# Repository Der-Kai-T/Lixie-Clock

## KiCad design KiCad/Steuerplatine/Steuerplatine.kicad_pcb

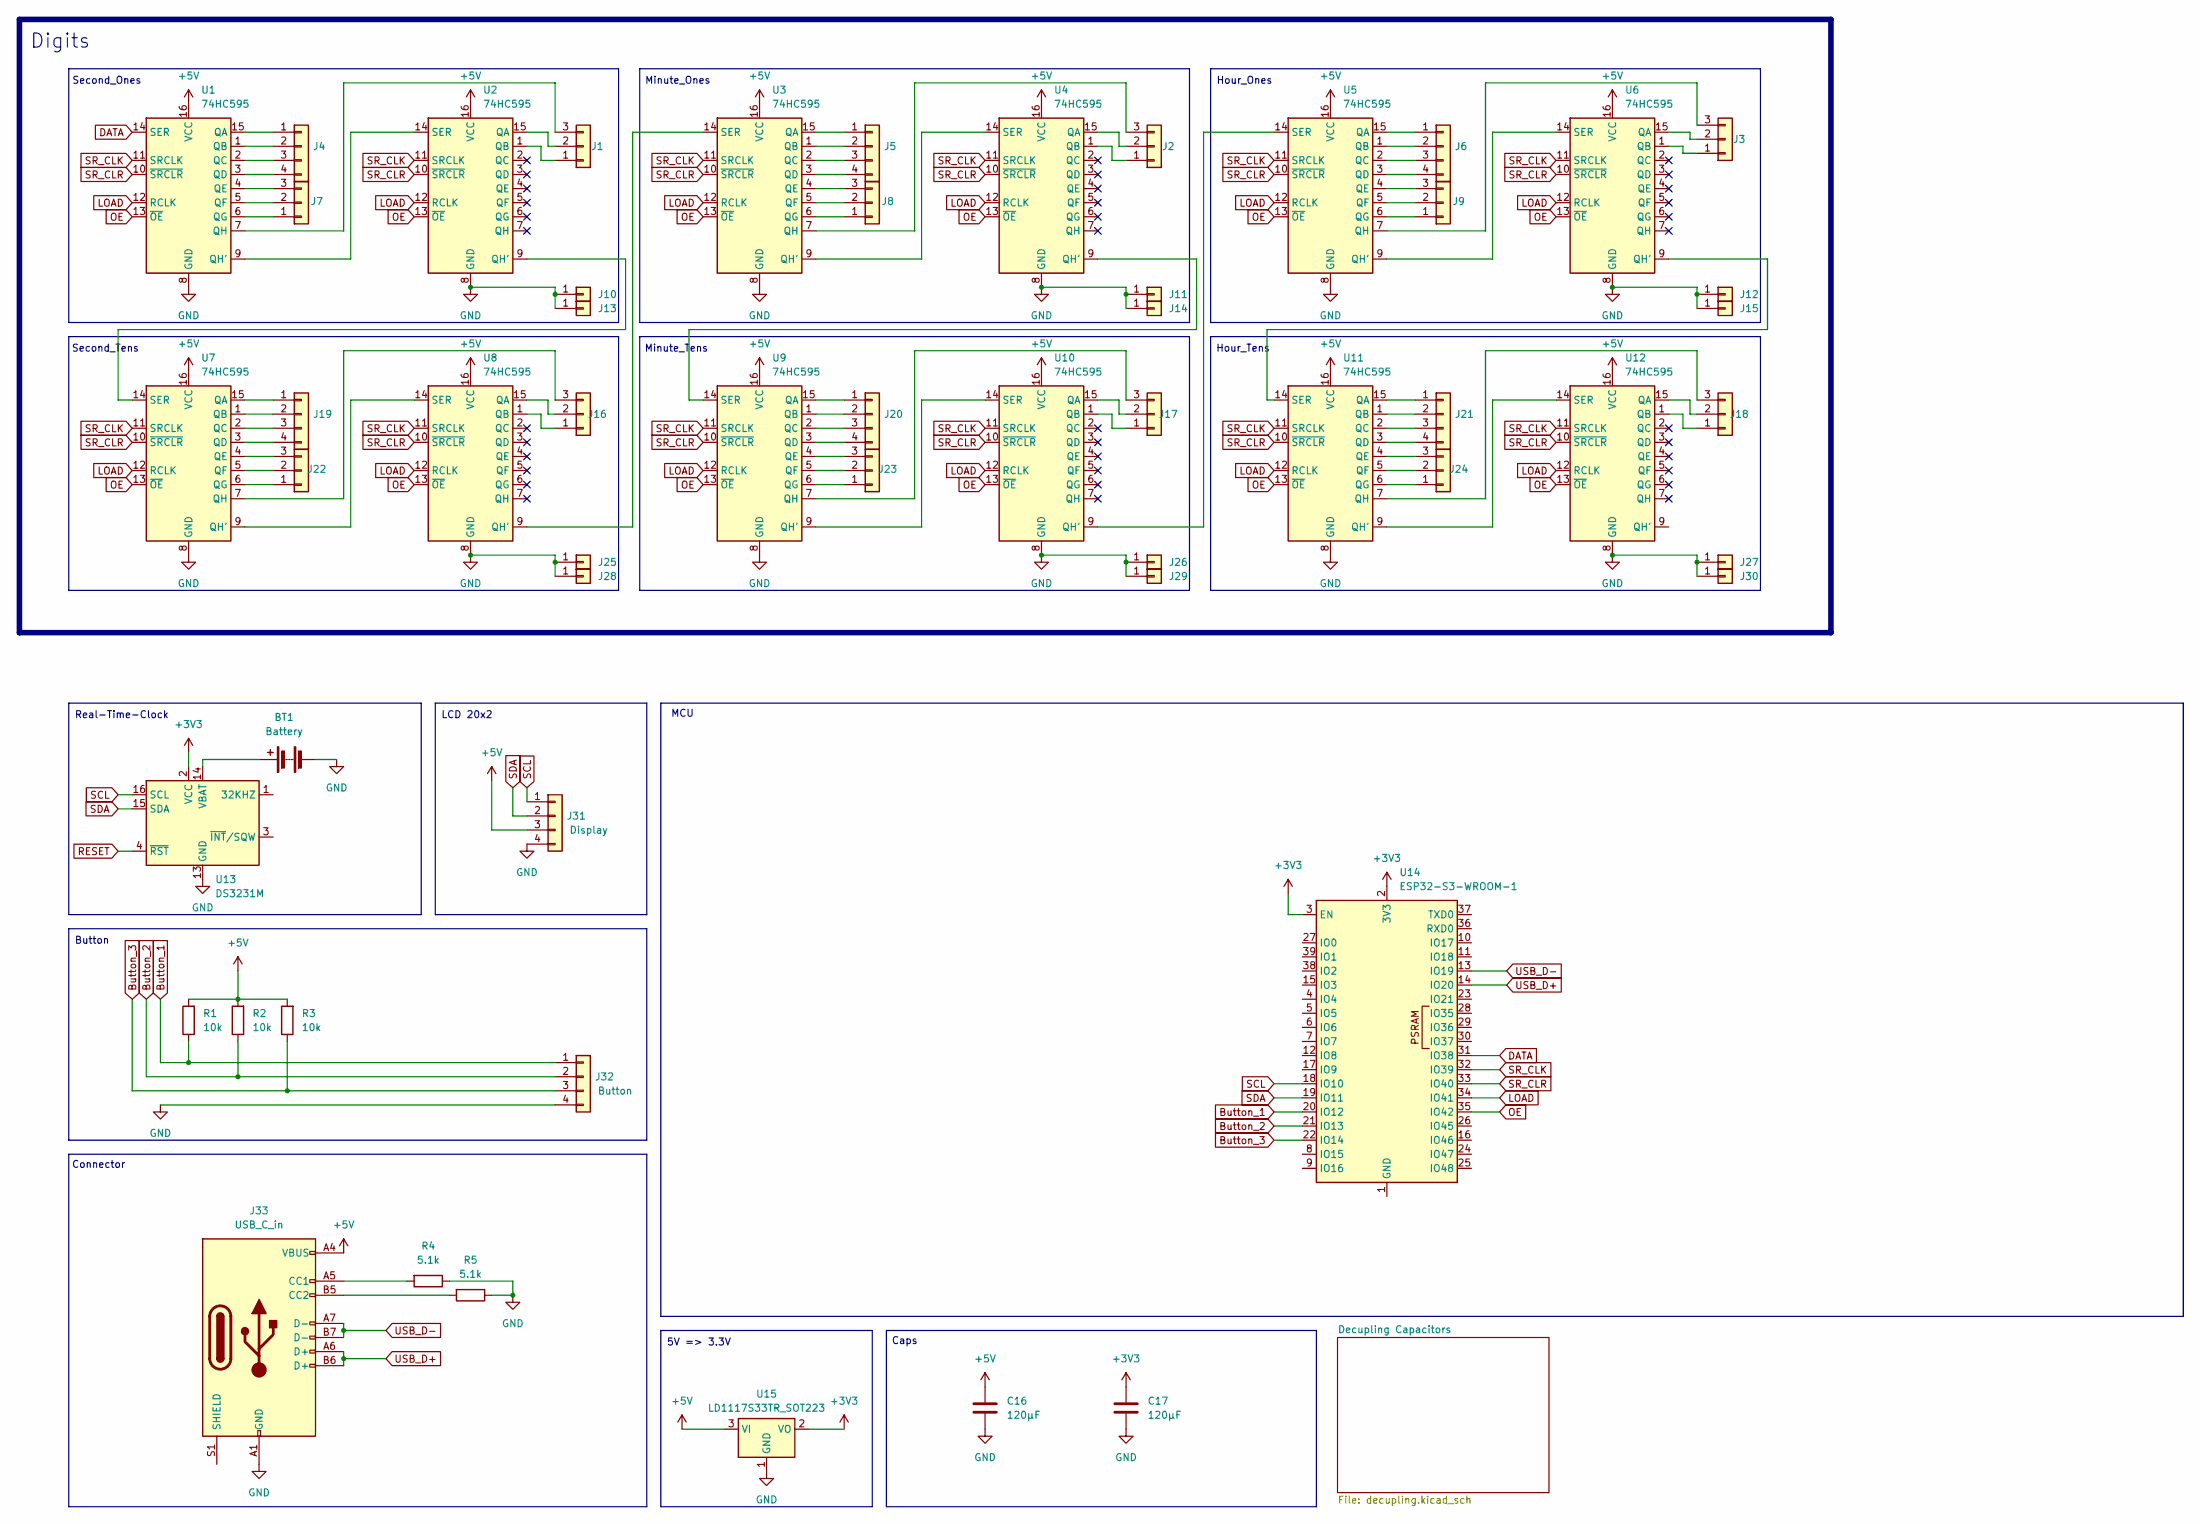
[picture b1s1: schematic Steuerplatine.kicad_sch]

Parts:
BT1: Battery; BatteryHolder_Multicomp_BC-2001_1x2032
C16, C17: 120µF; CP_Radial_D8.0mm_P3.50mm
J1, J2, J3, J7, J8, J9, J16, J17, J18, J22, J23, J24: Conn_01x03; PinSocket_1x03_P2.00mm_Vertical
J4, J5, J6, J19, J20, J21: Conn_01x04; PinSocket_1x04_P2.00mm_Vertical
J10, J11, J12, J13, J14, J15, J25, J26, J27, J28, J29, J30: GND; PinSocket_1x01_P2.00mm_Vertical
J31: Display; PinHeader_1x04_P2.54mm_Vertical
J32: Button; Molex_KK-254_AE-6410-04A_1x04_P2.54mm_Vertical
J33: USB_C_in; USB_C_Receptacle_GCT_USB4105-xx-A_16P_TopMnt_Horizontal
R1, R2, R3: 10k; R_1206_3216Metric_Pad1.30x1.75mm_HandSolder
R4, R5: 5.1k; R_1206_3216Metric_Pad1.30x1.75mm_HandSolder
U1, U2, U3, U4, U5, U6, U7, U8, U9, U10, U11, U12: 74HC595; SO-16_3.9x9.9mm_P1.27mm
U13: DS3231M; SOIC-16W_7.5x10.3mm_P1.27mm
U14: ESP32-S3-WROOM-1
U15: LD1117S33TR_SOT223; SOT-223-3_TabPin2

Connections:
+3V3: C17.1, U13.2 (VCC), U14.2 (3V3), U14.3 (EN), U15.2 (VO); also elsewhere on the board
+5V: C16.1, J31.3, J33.A4 (VBUS), J33.A9 (VBUS), J33.B4 (VBUS), J33.B9 (VBUS), R1.2, R2.2, R3.2, U1.16 (VCC), U2.16 (VCC), U3.16 (VCC), U4.16 (VCC), U5.16 (VCC), U6.16 (VCC), U7.16 (VCC), U8.16 (VCC), U9.16 (VCC), U10.16 (VCC), U11.16 (VCC), U12.16 (VCC), U15.3 (VI); also elsewhere on the board
Button_1: J32.1, R1.1, U14.20 (IO12)
Button_2: J32.2, R2.1, U14.21 (IO13)
Button_3: J32.3, R3.1, U14.22 (IO14)
DATA: U1.14 (SER), U14.31 (IO38)
GND: BT1.2 (-), C16.2, C17.2, J10.1, J11.1, J12.1, J13.1, J14.1, J15.1, J25.1, J26.1, J27.1, J28.1, J29.1, J30.1, J31.4, J32.4, J33.A1 (GND), J33.A12 (GND), J33.B1 (GND), J33.B12 (GND), R4.1, R5.1, U1.8 (GND), U2.8 (GND), U3.8 (GND), U4.8 (GND), U5.8 (GND), U6.8 (GND), U7.8 (GND), U8.8 (GND), U9.8 (GND), U10.8 (GND), U11.8 (GND), U12.8 (GND), U13.5 (GND), U13.6 (GND), U13.7 (GND), U13.8 (GND), U13.9 (GND), U13.10 (GND), U13.11 (GND), U13.12 (GND), U13.13 (GND), U15.1 (GND); also elsewhere on the board
LOAD: U1.12 (RCLK), U2.12 (RCLK), U3.12 (RCLK), U4.12 (RCLK), U5.12 (RCLK), U6.12 (RCLK), U7.12 (RCLK), U8.12 (RCLK), U9.12 (RCLK), U10.12 (RCLK), U11.12 (RCLK), U12.12 (RCLK), U14.34 (IO41)
unnamed: BT1.1 (+), U13.14 (VBAT)
unnamed: J1.1, U2.1 (QB)
unnamed: J1.2, U2.15 (QA)
unnamed: J1.3, U1.7 (QH)
unnamed: J2.1, U4.1 (QB)
unnamed: J2.2, U4.15 (QA)
unnamed: J2.3, U3.7 (QH)
unnamed: J3.1, U6.1 (QB)
unnamed: J3.2, U6.15 (QA)
unnamed: J3.3, U5.7 (QH)
unnamed: J4.1, U1.15 (QA)
unnamed: J4.2, U1.1 (QB)
unnamed: J4.3, U1.2 (QC)
unnamed: J4.4, U1.3 (QD)
unnamed: J5.1, U3.15 (QA)
unnamed: J5.2, U3.1 (QB)
unnamed: J5.3, U3.2 (QC)
unnamed: J5.4, U3.3 (QD)
unnamed: J6.1, U5.15 (QA)
unnamed: J6.2, U5.1 (QB)
unnamed: J6.3, U5.2 (QC)
unnamed: J6.4, U5.3 (QD)
unnamed: J7.1, U1.6 (QG)
unnamed: J7.2, U1.5 (QF)
unnamed: J7.3, U1.4 (QE)
unnamed: J8.1, U3.6 (QG)
unnamed: J8.2, U3.5 (QF)
unnamed: J8.3, U3.4 (QE)
unnamed: J9.1, U5.6 (QG)
unnamed: J9.2, U5.5 (QF)
unnamed: J9.3, U5.4 (QE)
unnamed: J16.1, U8.1 (QB)
unnamed: J16.2, U8.15 (QA)
unnamed: J16.3, U7.7 (QH)
unnamed: J17.1, U10.1 (QB)
unnamed: J17.2, U10.15 (QA)
unnamed: J17.3, U9.7 (QH)
unnamed: J18.1, U12.1 (QB)
unnamed: J18.2, U12.15 (QA)
unnamed: J18.3, U11.7 (QH)
unnamed: J19.1, U7.15 (QA)
unnamed: J19.2, U7.1 (QB)
unnamed: J19.3, U7.2 (QC)
unnamed: J19.4, U7.3 (QD)
unnamed: J20.1, U9.15 (QA)
unnamed: J20.2, U9.1 (QB)
unnamed: J20.3, U9.2 (QC)
unnamed: J20.4, U9.3 (QD)
unnamed: J21.1, U11.15 (QA)
unnamed: J21.2, U11.1 (QB)
unnamed: J21.3, U11.2 (QC)
unnamed: J21.4, U11.3 (QD)
unnamed: J22.1, U7.6 (QG)
unnamed: J22.2, U7.5 (QF)
unnamed: J22.3, U7.4 (QE)
unnamed: J23.1, U9.6 (QG)
unnamed: J23.2, U9.5 (QF)
unnamed: J23.3, U9.4 (QE)
unnamed: J24.1, U11.6 (QG)
unnamed: J24.2, U11.5 (QF)
unnamed: J24.3, U11.4 (QE)
unnamed: J33.A5 (CC1), R4.2
unnamed: J33.B5 (CC2), R5.2
unnamed: U1.9 (QH'), U2.14 (SER)
unnamed: U2.9 (QH'), U7.14 (SER)
unnamed: U3.9 (QH'), U4.14 (SER)
unnamed: U3.14 (SER), U8.9 (QH')
unnamed: U4.9 (QH'), U9.14 (SER)
unnamed: U5.9 (QH'), U6.14 (SER)
unnamed: U7.9 (QH'), U8.14 (SER)
unnamed: U5.14 (SER), U10.9 (QH')
unnamed: U9.9 (QH'), U10.14 (SER)
unnamed: U11.9 (QH'), U12.14 (SER)
unnamed: U6.9 (QH'), U11.14 (SER)
unnamed: U14.1 (GND), U14.40 (GND), U14.41 (GND)
OE: U1.13 (~OE), U2.13 (~OE), U3.13 (~OE), U4.13 (~OE), U5.13 (~OE), U6.13 (~OE), U7.13 (~OE), U8.13 (~OE), U9.13 (~OE), U10.13 (~OE), U11.13 (~OE), U12.13 (~OE), U14.35 (IO42)
RESET: U13.4 (~RST)
SCL: J31.1, U13.16 (SCL), U14.18 (IO10)
SDA: J31.2, U13.15 (SDA), U14.19 (IO11)
SR_CLK: U1.11 (SRCLK), U2.11 (SRCLK), U3.11 (SRCLK), U4.11 (SRCLK), U5.11 (SRCLK), U6.11 (SRCLK), U7.11 (SRCLK), U8.11 (SRCLK), U9.11 (SRCLK), U10.11 (SRCLK), U11.11 (SRCLK), U12.11 (SRCLK), U14.32 (IO39)
SR_CLR: U1.10 (~SRCLR), U2.10 (~SRCLR), U3.10 (~SRCLR), U4.10 (~SRCLR), U5.10 (~SRCLR), U6.10 (~SRCLR), U7.10 (~SRCLR), U8.10 (~SRCLR), U9.10 (~SRCLR), U10.10 (~SRCLR), U11.10 (~SRCLR), U12.10 (~SRCLR), U14.33 (IO40)
USB_D+: J33.A6 (D+), J33.B6 (D+), U14.14 (IO20)
USB_D-: J33.A7 (D-), J33.B7 (D-), U14.13 (IO19)

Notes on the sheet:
5V => 3.3V
Caps
Button
Hour_Tens
LCD 20x2
Digits
Connector
Minute_Ones
Minute_Tens
Second_Ones
Second_Tens
Hour_Ones
Real-Time-Clock
MCU

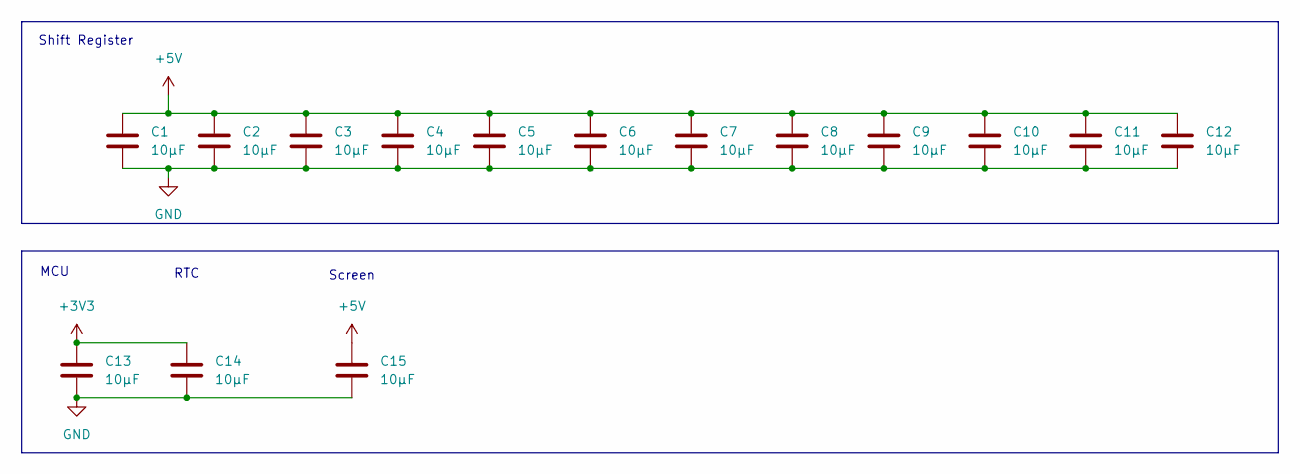
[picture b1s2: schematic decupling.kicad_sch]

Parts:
C1, C2, C3, C4, C5, C6, C7, C8, C9, C10, C11, C12, C13, C14, C15: 10µF; C_0805_2012Metric

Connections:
+3V3: C13.1, C14.1; also elsewhere on the board
+5V: C1.1, C2.1, C3.1, C4.1, C5.1, C6.1, C7.1, C8.1, C9.1, C10.1, C11.1, C12.1, C15.1; also elsewhere on the board
GND: C1.2, C2.2, C3.2, C4.2, C5.2, C6.2, C7.2, C8.2, C9.2, C10.2, C11.2, C12.2, C13.2, C14.2, C15.2; also elsewhere on the board

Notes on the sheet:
Shift Register
MCU
RTC
Screen

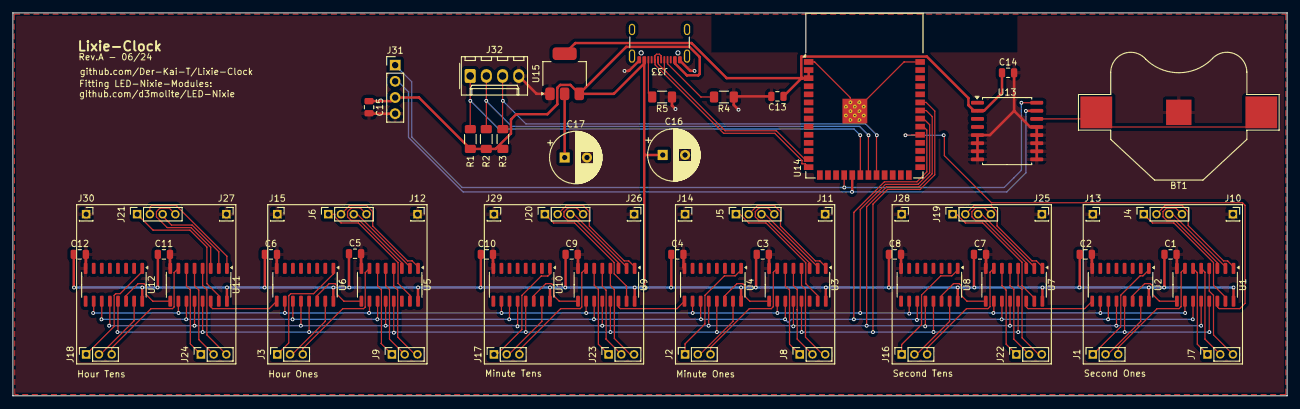
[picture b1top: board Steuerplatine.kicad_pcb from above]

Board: 2 copper layers, 200.0 x 60.1 mm, 71 parts (0 on the bottom side), 90 nets.

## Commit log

2024-07-13 Fix DRU-Errors
